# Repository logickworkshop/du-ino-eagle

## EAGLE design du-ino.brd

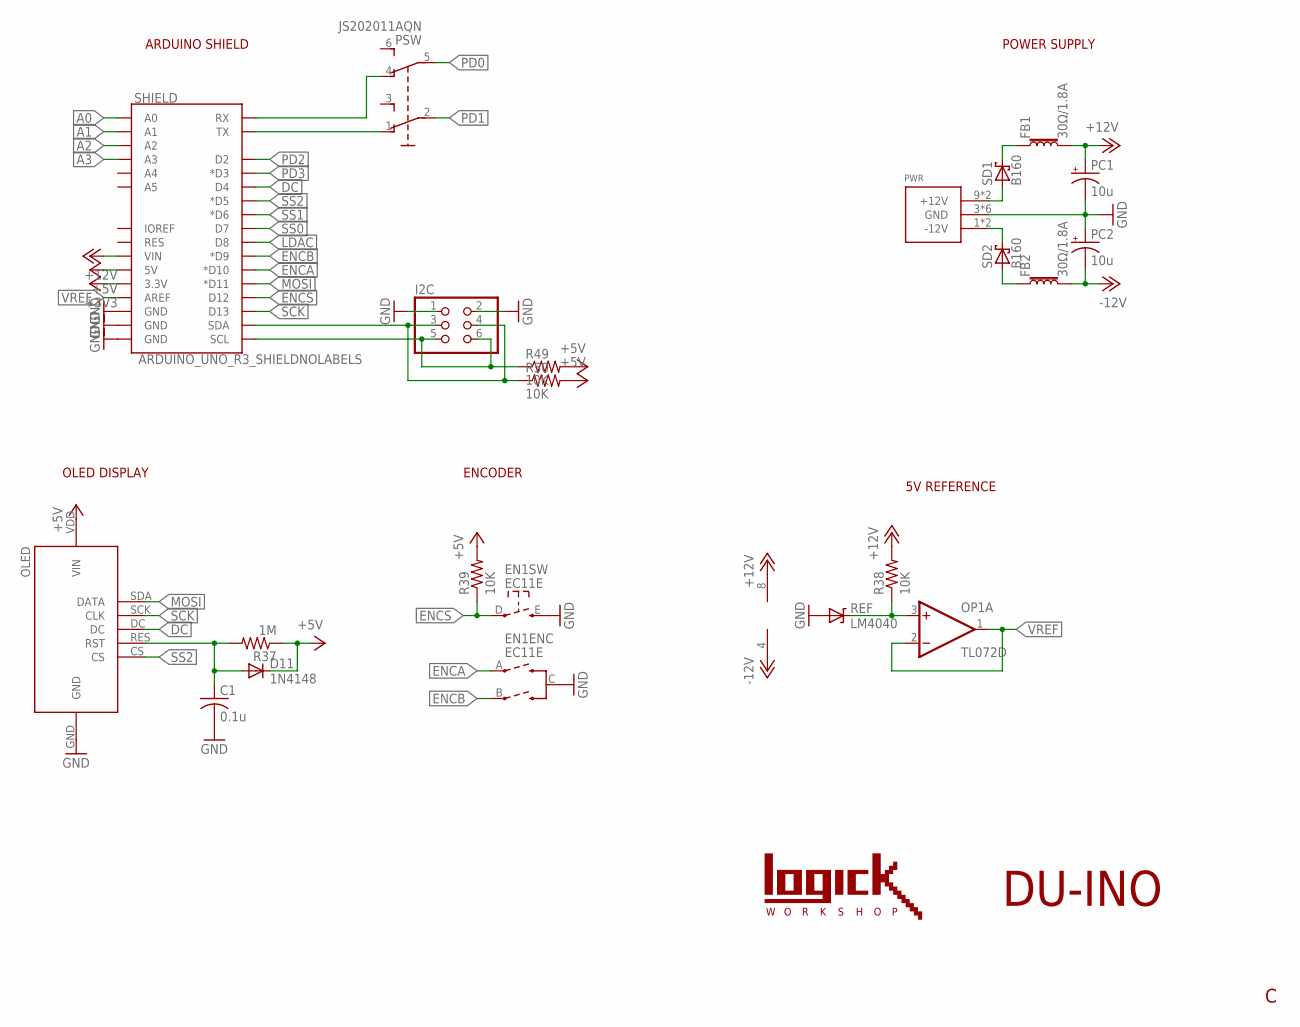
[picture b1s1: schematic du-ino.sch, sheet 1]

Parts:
C1: 0.1u; C0603
D11: 1N4148; SOD123
EN1: EC11E
FB1, FB2: 30Ω/1.8A; 0603
I2C: PINHD-2X3; 2X03
OLED: OLED-SAMIORE
OP1: TL072D; SO08
PC1, PC2: 10u; PANASONIC_B
PSW: JS202011AQN
PWR: POWER_SIMPLE10; POWER_10
R37: 1M; R0603
R38, R39, R49, R50: 10K; R0603
REF: LM4040; SOT23
SD1, SD2: B160; SMB
SHIELD: ARDUINO_UNO_R3_SHIELDNOLABELS; UNO_R3_SHIELD_NOLABELS

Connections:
+3V3: SHIELD.3.3V; also elsewhere on the board
+5V: D11.C, OLED.VDD (VIN), R37.1, R39.2, R49.2, R50.2, SHIELD.5V; also elsewhere on the board
+12V: FB1.2, OP1.8 (V+), PC1.+, R38.2, SHIELD.VIN; also elsewhere on the board
-12V: FB2.2, OP1.4 (V-), PC2.-; also elsewhere on the board
A0: SHIELD.A0; also elsewhere on the board
A1: SHIELD.A1; also elsewhere on the board
A2: SHIELD.A2; also elsewhere on the board
A3: SHIELD.A3; also elsewhere on the board
DC: OLED.DC, SHIELD.D4
ENCA: EN1.A, SHIELD.D10 (*D10)
ENCB: EN1.B, SHIELD.D9 (*D9)
ENCS: EN1.D (1), R39.1, SHIELD.D12
GND: C1.2, EN1.C, EN1.E (3), I2C.1, I2C.2, OLED.GND, PC1.-, PC2.+, PWR.3 (GND), PWR.4 (GND), PWR.5 (GND), PWR.6 (GND), PWR.7 (GND), PWR.8 (GND), REF.2 (A), SHIELD.GND@0 (GND), SHIELD.GND@1 (GND), SHIELD.GND@2 (GND); also elsewhere on the board
LDAC: SHIELD.D8; also elsewhere on the board
MOSI: OLED.SDA (DATA), SHIELD.D11 (*D11); also elsewhere on the board
unnamed: C1.1, D11.A, OLED.RES (RST), R37.2
unnamed: PWR.1 (-12V), PWR.2 (-12V), SD2.C
unnamed: FB2.1, SD2.A
unnamed: FB1.1, SD1.C
unnamed: PWR.9 (+12V), PWR.10 (+12V), SD1.A
unnamed: PSW.1 (O), SHIELD.TX
unnamed: PSW.4 (O1), SHIELD.RX
unnamed: OP1.3 (+IN), R38.1, REF.1 (C)
PD0: PSW.5 (P1); also elsewhere on the board
PD1: PSW.2; also elsewhere on the board
PD2: SHIELD.D2; also elsewhere on the board
PD3: SHIELD.D3 (*D3); also elsewhere on the board
SCK: OLED.SCK (CLK), SHIELD.D13; also elsewhere on the board
SCL: I2C.5, I2C.6, R49.1, SHIELD.SCL
SDA: I2C.3, I2C.4, R50.1, SHIELD.SDA
SS0: SHIELD.D7; also elsewhere on the board
SS1: SHIELD.D6 (*D6); also elsewhere on the board
SS2: OLED.CS, SHIELD.D5 (*D5)
VREF: OP1.1 (OUT), OP1.2 (-IN), SHIELD.AREF; also elsewhere on the board

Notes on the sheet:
ARDUINO SHIELD
OLED DISPLAY
ENCODER
5V REFERENCE
POWER SUPPLY
DU-INO

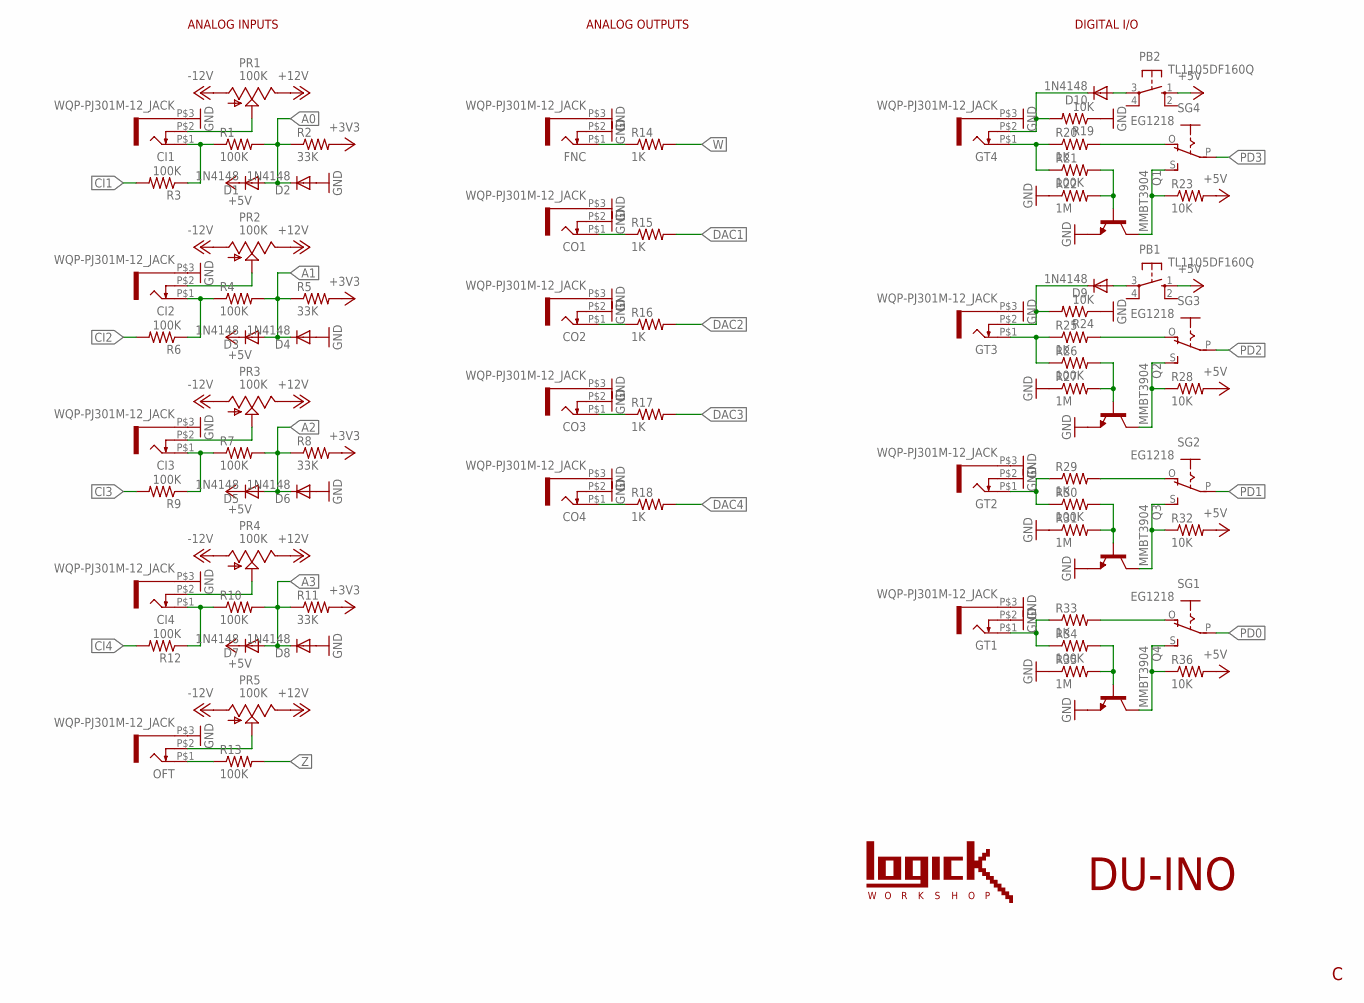
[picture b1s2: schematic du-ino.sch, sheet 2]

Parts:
CI1, CI2, CI3, CI4: WQP-PJ301M-12_JACK
CO1, CO2, CO3, CO4: WQP-PJ301M-12_JACK
D1, D2, D3, D4, D5, D6, D7, D8, D9, D10: 1N4148; SOD123
FNC: WQP-PJ301M-12_JACK
GT1, GT2, GT3, GT4: WQP-PJ301M-12_JACK
OFT: WQP-PJ301M-12_JACK
PB1, PB2: TL1105DF160Q; B3F-10XX
PR1, PR2, PR3, PR4, PR5: 100K; R0904N
Q1, Q2, Q3, Q4: MMBT3904; SOT23-BEC
R1, R3, R4, R6, R7, R9, R10, R12, R13, R21, R26, R30, R34: 100K; R0603
R2, R5, R8, R11: 33K; R0603
R14, R15, R16, R17, R18, R20, R25, R29, R33: 1K; R0603
R19, R23, R24, R28, R32, R36: 10K; R0603
R22, R27, R31, R35: 1M; R0603
SG1, SG2, SG3, SG4: EG1218

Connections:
+3V3: R2.2, R5.2, R8.2, R11.2; also elsewhere on the board
+5V: D1.C, D3.C, D5.C, D7.C, PB1.1 (S), PB2.1 (S), R23.2, R28.2, R32.2, R36.2; also elsewhere on the board
+12V: PR1.3 (E), PR2.3 (E), PR3.3 (E), PR4.3 (E), PR5.3 (E); also elsewhere on the board
-12V: PR1.1 (A), PR2.1 (A), PR3.1 (A), PR4.1 (A), PR5.1 (A); also elsewhere on the board
A0: D1.A, D2.C, R1.2, R2.1; also elsewhere on the board
A1: D3.A, D4.C, R4.2, R5.1; also elsewhere on the board
A2: D5.A, D6.C, R7.2, R8.1; also elsewhere on the board
A3: D7.A, D8.C, R10.2, R11.1; also elsewhere on the board
CI1: R3.2; also elsewhere on the board
CI2: R6.2; also elsewhere on the board
CI3: R9.2; also elsewhere on the board
CI4: R12.2; also elsewhere on the board
DAC1: R15.2; also elsewhere on the board
DAC2: R16.2; also elsewhere on the board
DAC3: R17.2; also elsewhere on the board
DAC4: R18.2; also elsewhere on the board
GND: CI1.P$3 (1), CI2.P$3 (1), CI3.P$3 (1), CI4.P$3 (1), CO1.P$2 (3), CO1.P$3 (1), CO2.P$2 (3), CO2.P$3 (1), CO3.P$2 (3), CO3.P$3 (1), CO4.P$2 (3), CO4.P$3 (1), D2.A, D4.A, D6.A, D8.A, FNC.P$2 (3), FNC.P$3 (1), GT1.P$2 (3), GT1.P$3 (1), GT2.P$2 (3), GT2.P$3 (1), GT3.P$3 (1), GT4.P$3 (1), OFT.P$3 (1), Q1.E, Q2.E, Q3.E, Q4.E, R19.1, R22.1, R24.1, R27.1, R31.1, R35.1; also elsewhere on the board
unnamed: CI1.P$2 (3), PR1.2 (S)
unnamed: CI2.P$2 (3), PR2.2 (S)
unnamed: CI3.P$2 (3), PR3.2 (S)
unnamed: CI4.P$2 (3), PR4.2 (S)
unnamed: OFT.P$2 (3), PR5.2 (S)
unnamed: OFT.P$1 (2), R13.1
unnamed: CI1.P$1 (2), R1.1, R3.1
unnamed: CI2.P$1 (2), R4.1, R6.1
unnamed: CI3.P$1 (2), R7.1, R9.1
unnamed: CI4.P$1 (2), R10.1, R12.1
unnamed: GT1.P$1 (2), R33.1, R34.1
unnamed: FNC.P$1 (2), R14.1
unnamed: GT3.P$1 (2), R25.1, R26.1
unnamed: GT4.P$1 (2), R20.1, R21.1
unnamed: GT2.P$1 (2), R29.1, R30.1
unnamed: CO1.P$1 (2), R15.1
unnamed: CO2.P$1 (2), R16.1
unnamed: CO4.P$1 (2), R18.1
unnamed: CO3.P$1 (2), R17.1
unnamed: R25.2, SG3.O
unnamed: R20.2, SG4.O
unnamed: R29.2, SG2.O
unnamed: R33.2, SG1.O
unnamed: Q2.C, R28.1, SG3.S
unnamed: Q1.B, R21.2, R22.2
unnamed: Q1.C, R23.1, SG4.S
unnamed: Q3.B, R30.2, R31.2
unnamed: Q2.B, R26.2, R27.2
unnamed: Q3.C, R32.1, SG2.S
unnamed: Q4.B, R34.2, R35.2
unnamed: Q4.C, R36.1, SG1.S
unnamed: D9.A, PB1.3
unnamed: D9.C, GT3.P$2 (3), R24.2
unnamed: D10.A, PB2.3
unnamed: D10.C, GT4.P$2 (3), R19.2
PD0: SG1.P; also elsewhere on the board
PD1: SG2.P; also elsewhere on the board
PD2: SG3.P; also elsewhere on the board
PD3: SG4.P; also elsewhere on the board
W: R14.2; also elsewhere on the board
Z: R13.2; also elsewhere on the board

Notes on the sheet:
ANALOG INPUTS
ANALOG OUTPUTS
DIGITAL I/O
DU-INO

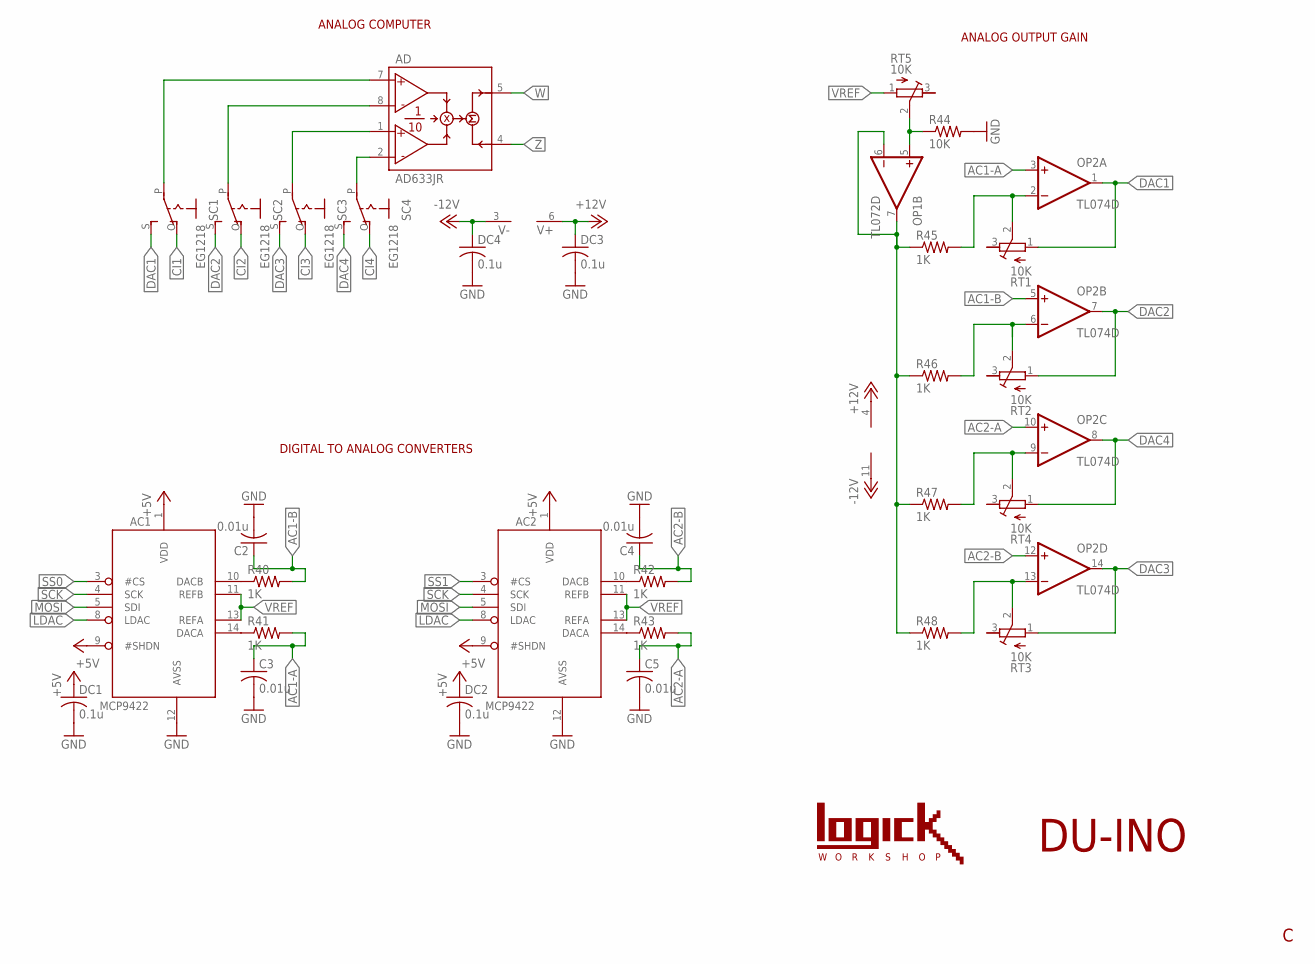
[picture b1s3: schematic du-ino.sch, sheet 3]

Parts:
AC1, AC2: MCP4922E/SL; SO14
AD: AD633JR; SO8
C2, C3, C4, C5: 0.01u; C0603
DC1, DC2, DC3, DC4: 0.1u; C0603
OP1: TL072D; SO08
OP2: TL074D; SO14
R40, R41, R42, R43, R45, R46, R47, R48: 1K; R0603
R44: 10K; R0603
RT1, RT2, RT3, RT4, RT5: 10K; RTRIM3296W
SC1, SC2, SC3, SC4: EG1218

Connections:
+5V: AC1.1 (VDD), AC1.9 (#SHDN), AC2.1 (VDD), AC2.9 (#SHDN), DC1.1, DC2.1; also elsewhere on the board
+12V: AD.6 (V+), DC3.1, OP2.4 (V+); also elsewhere on the board
-12V: AD.3 (V-), DC4.1, OP2.11 (V-); also elsewhere on the board
AC1-A: C3.1, OP2.3 (+IN), R41.2
AC1-B: C2.1, OP2.5 (+IN), R40.2
AC2-A: C5.1, OP2.10 (+IN), R43.2
AC2-B: C4.1, OP2.12 (+IN), R42.2
CI1: SC1.O; also elsewhere on the board
CI2: SC2.O; also elsewhere on the board
CI3: SC3.O; also elsewhere on the board
CI4: SC4.O; also elsewhere on the board
DAC1: OP2.1 (OUT), RT1.1 (A), SC1.S; also elsewhere on the board
DAC2: OP2.7 (OUT), RT2.1 (A), SC2.S; also elsewhere on the board
DAC3: OP2.14 (OUT), RT3.1 (A), SC3.S; also elsewhere on the board
DAC4: OP2.8 (OUT), RT4.1 (A), SC4.S; also elsewhere on the board
GND: AC1.12 (AVSS), AC2.12 (AVSS), C2.2, C3.2, C4.2, C5.2, DC1.2, DC2.2, DC3.2, DC4.2, R44.2; also elsewhere on the board
LDAC: AC1.8 (LDAC), AC2.8 (LDAC); also elsewhere on the board
MOSI: AC1.5 (SDI), AC2.5 (SDI); also elsewhere on the board
unnamed: AD.2 (Y2), SC4.P
unnamed: AD.1 (Y1), SC3.P
unnamed: AD.8 (X2), SC2.P
unnamed: AD.7 (X1), SC1.P
unnamed: OP2.2 (-IN), R45.2, RT1.2 (S)
unnamed: OP2.6 (-IN), R46.2, RT2.2 (S)
unnamed: OP1.6 (-IN), OP1.7 (OUT), R45.1, R46.1, R47.1, R48.1
unnamed: OP2.9 (-IN), R47.2, RT4.2 (S)
unnamed: OP2.13 (-IN), R48.2, RT3.2 (S)
unnamed: AC1.10 (DACB), R40.1
unnamed: AC1.14 (DACA), R41.1
unnamed: AC2.10 (DACB), R42.1
unnamed: AC2.14 (DACA), R43.1
unnamed: OP1.5 (+IN), R44.1, RT5.2 (S)
SCK: AC1.4 (SCK), AC2.4 (SCK); also elsewhere on the board
SS0: AC1.3 (#CS); also elsewhere on the board
SS1: AC2.3 (#CS); also elsewhere on the board
VREF: AC1.11 (REFB), AC1.13 (REFA), AC2.11 (REFB), AC2.13 (REFA), RT5.1 (A); also elsewhere on the board
W: AD.5 (W); also elsewhere on the board
Z: AD.4 (Z); also elsewhere on the board

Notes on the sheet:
ANALOG COMPUTER
DIGITAL TO ANALOG CONVERTERS
ANALOG OUTPUT GAIN
DU-INO

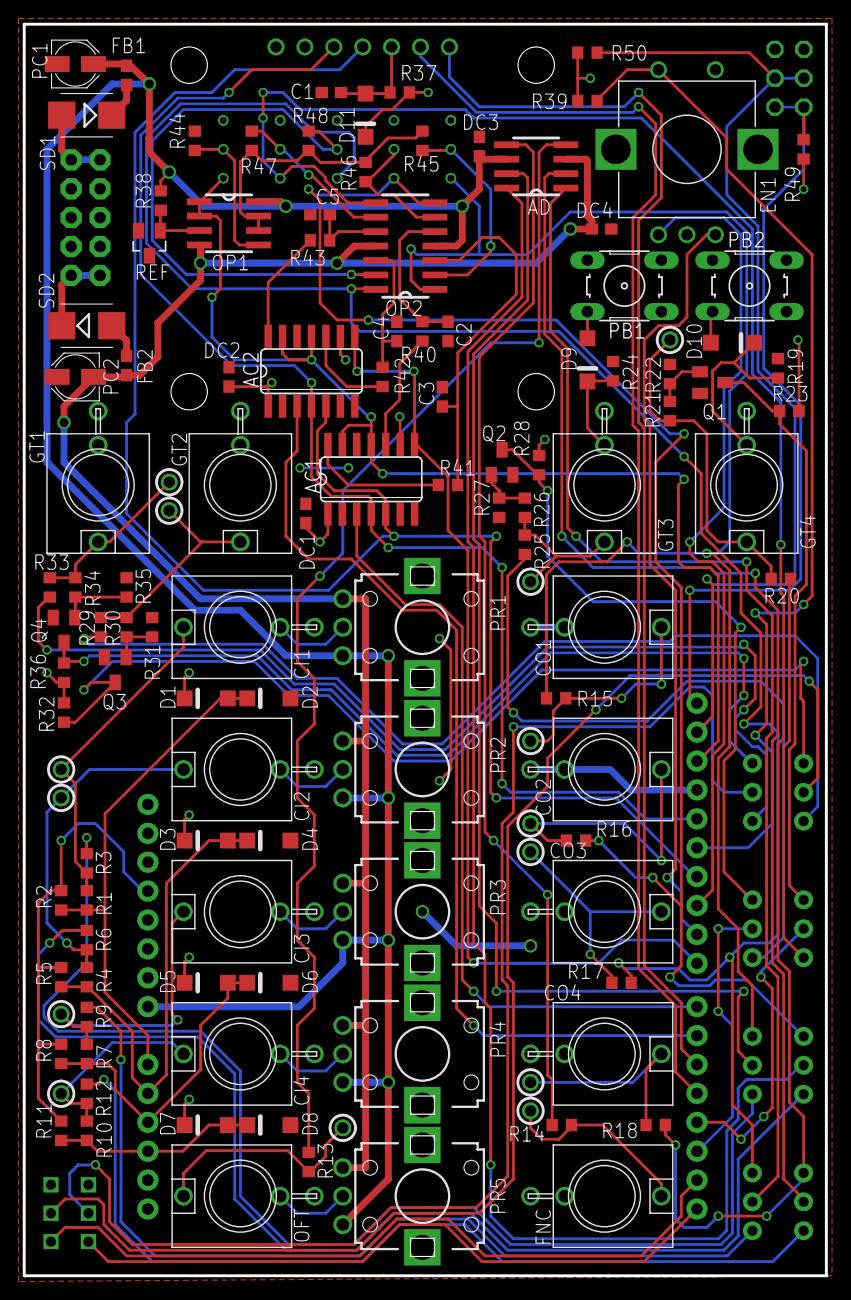
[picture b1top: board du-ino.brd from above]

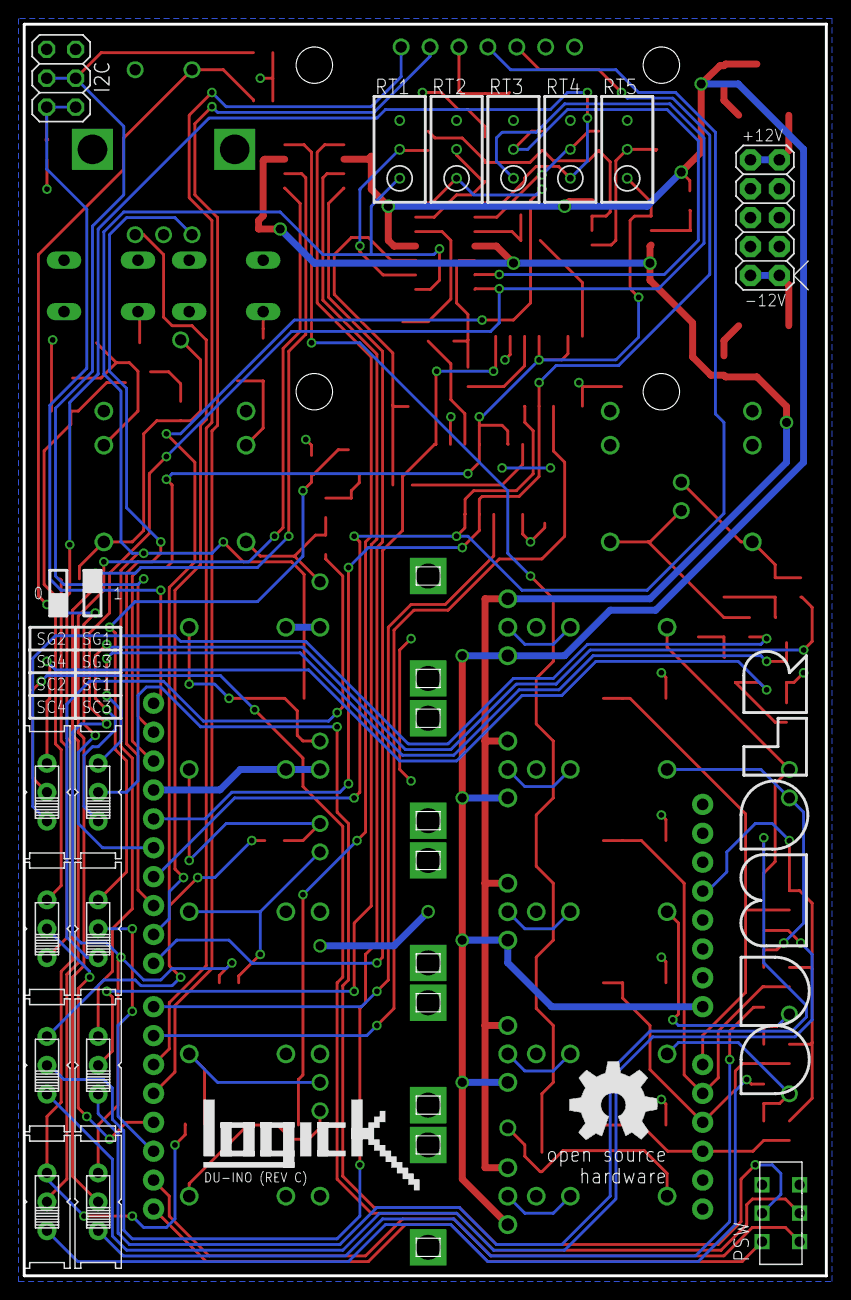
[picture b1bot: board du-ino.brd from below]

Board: 2 copper layers, 70.5 x 110.0 mm, 127 parts (17 on the bottom side), 97 nets.

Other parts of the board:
U$1: OSHW_8MM

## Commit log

2018-09-07 Initial commit of Revision C design files.
2020-07-25 Add front panel SVG.

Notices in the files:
parts and their libraries:
SparkFun-Coils: Licensing: Creative Commons ShareAlike 4.0 International - https://creativecommons.org/licenses/by-sa/4.0
